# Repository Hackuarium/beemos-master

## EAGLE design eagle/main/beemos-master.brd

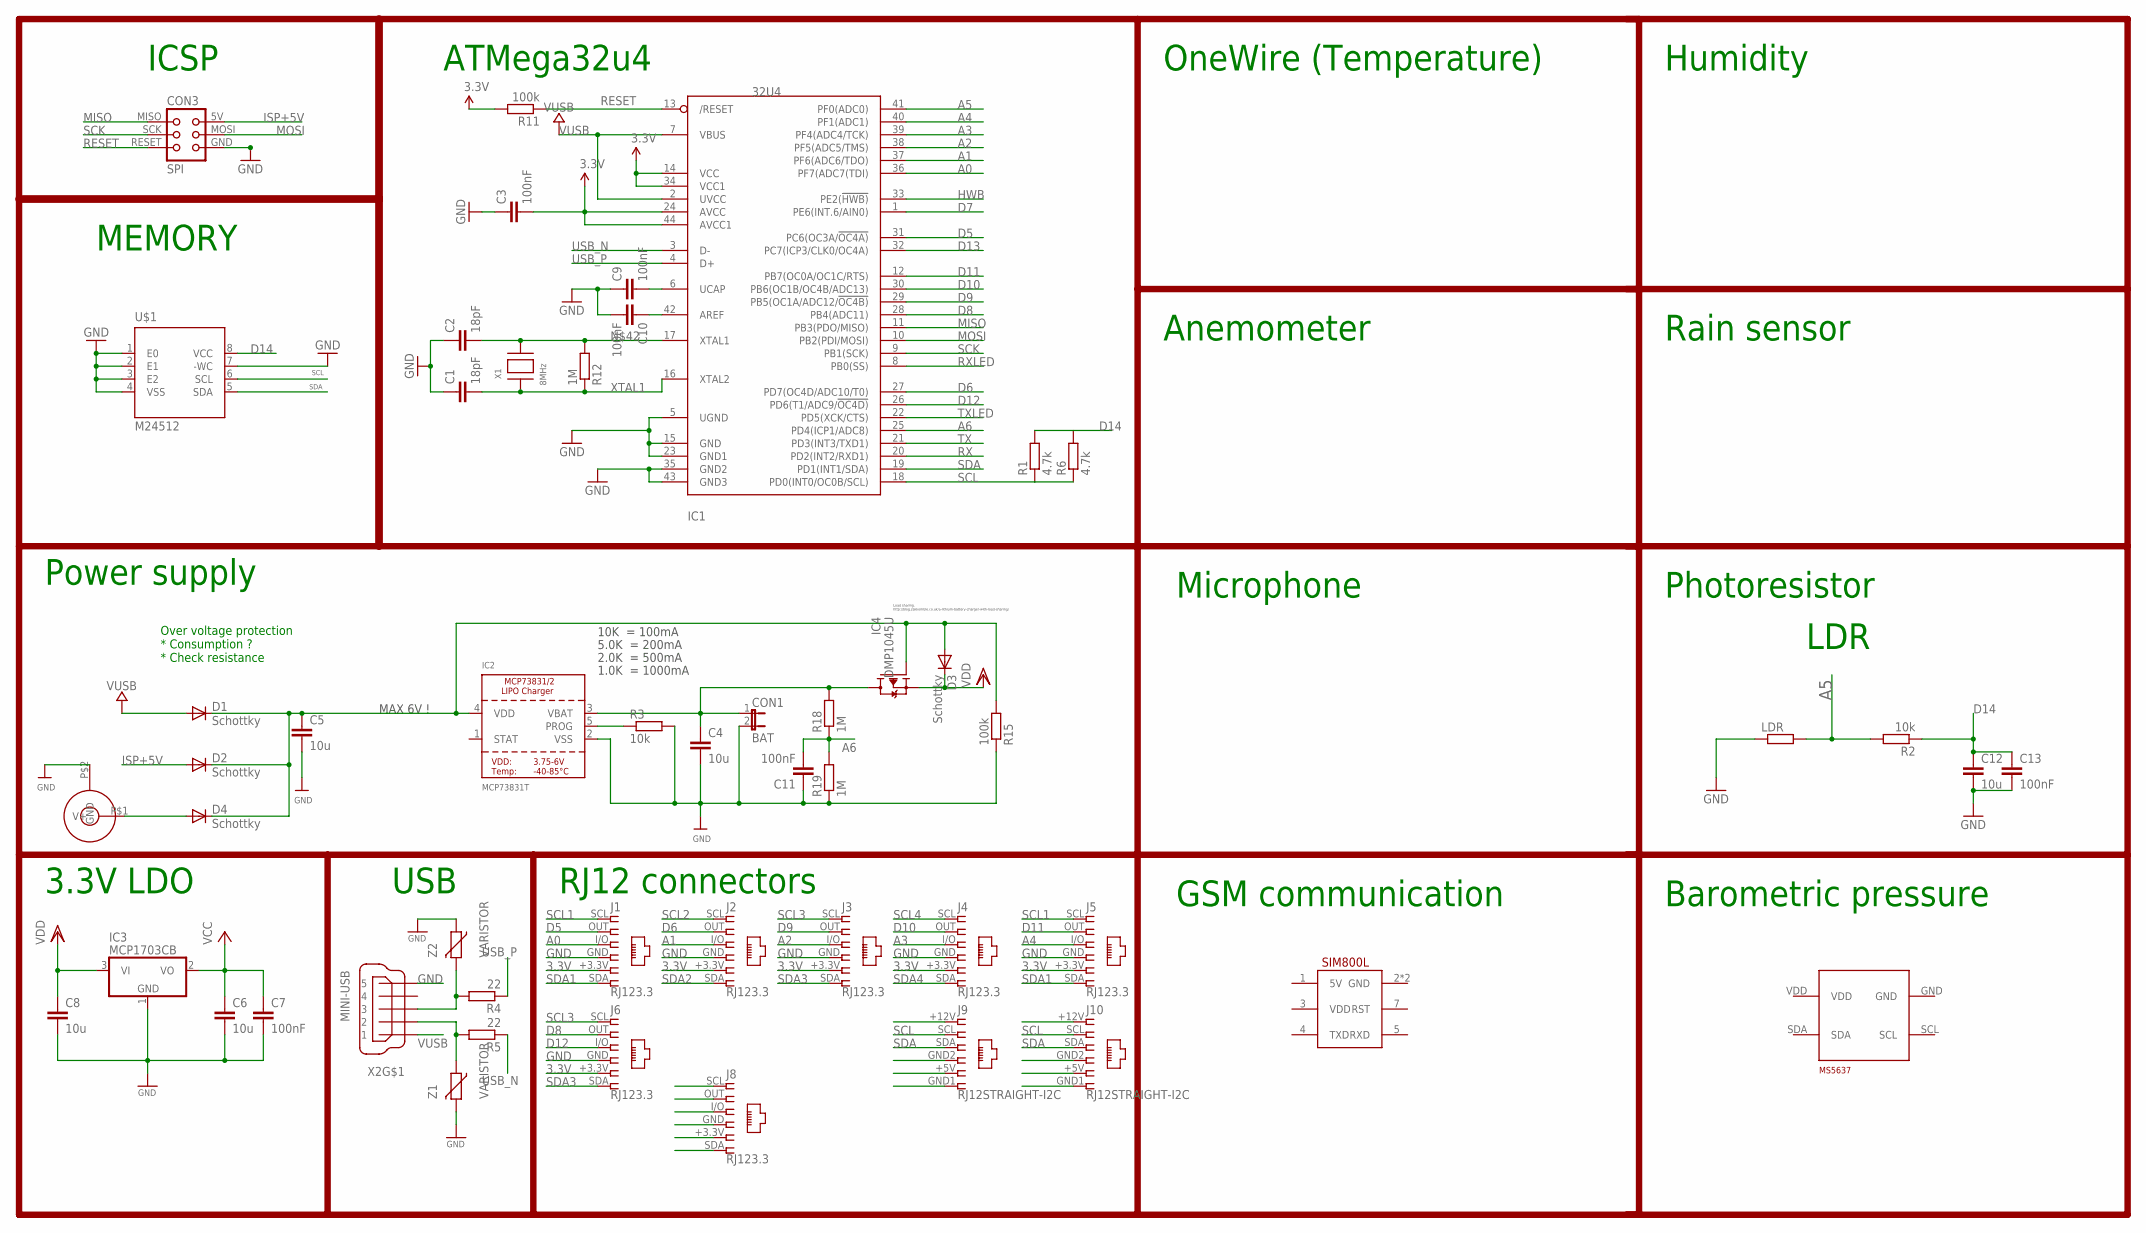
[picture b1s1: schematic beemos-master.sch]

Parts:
C1, C2: 18pF; C0805K; MPN 77-VJ1206A180JXXPBC; LCSC C1797
C3, C7, C9, C10, C11, C13: 100nF; C0805K; MPN 80-C1206C104K5R; LCSC C49678
C4, C5, C6, C8, C12: 10u; C0805K; MPN 77-VJ1206V106ZXQTBC; LCSC C15850
CON1: BAT; JP1
CON2: JACK_DC_BARREL; DC_BARREL
CON3: SPI; TC2030-MCP-NL
D1, D2, D3, D4: Schottky; SOD123; MPN 621-1N5819HW-F; LCSC C82544
IC1: 32U4; TQFP44; MPN 556-ATMEGA32U4RC-AU; LCSC C44854
IC2: MCP73831T; SOT23-5; MPN 579-MCP73831T-3ACIOT; LCSC C14879
IC3: MCP1703CB; SOT23; LCSC C53352
IC4: DMP1045U; SOT-23; MPN 621-DMP1045U-7; LCSC C96613
J1, J2, J3, J4, J5, J6, J8: RJ123.3; RJ12-STRAIGHT-3.3
J9, J10: RJ12STRAIGHT-I2C; RJ12-STRAIGHT-I2C
LDR: R-EU_0207/2V; 0207/2V
R1, R6: 4.7k; R0805
R2: 10k; R0805; MPN RC1206FR-07100KL; LCSC C17407
R3: 10k; R0805; LCSC C17414
R4, R5: 22; R0805; LCSC C17561
R11, R15: 100k; R0805; MPN RC1206FR-07100KL; LCSC C17407
R12, R18, R19: 1M; R0805; LCSC C17514
U$1: M24512; SO8
U$6: SIM800L; SIP
U$7: MS5637
X1: 8MHz; NX6035; MPN 729-F60800010; LCSC C122522
X2: MINI-USB; 32005-201; MPN 649-10033526-N3212LF; LCSC C46391
Z1, Z2: VARISTOR; CT/CN0805; LCSC C79709

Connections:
3.3V: C3.2, C6.1, C7.1, IC1.14 (VCC), IC1.24 (AVCC), IC1.34 (VCC1), IC1.44 (AVCC1), IC3.2 (VO), J1.+3.3V (5), J2.+3.3V (5), J3.+3.3V (5), J4.+3.3V (5), J5.+3.3V (5), J6.+3.3V (5), R11.2
A0: IC1.36 (PF7(ADC7(TDI)), J1.I/O (3)
A1: IC1.37 (PF6(ADC6/TDO)), J2.I/O (3)
A2: IC1.38 (PF5(ADC5/TMS)), J3.I/O (3)
A3: IC1.39 (PF4(ADC4/TCK)), J4.I/O (3)
A4: IC1.40 (PF1(ADC1)), J5.I/O (3)
A5: IC1.41 (PF0(ADC0)), LDR.2, R2.2
A6: C11.2, IC1.25 (PD4(ICP1/ADC8)), R18.1, R19.2
AREF: C10.1, IC1.42 (AREF)
D5: IC1.31 (PC6(OC3A/!OC4A)), J1.OUT (2)
D6: IC1.27 (PD7(OC4D/ADC10/T0)), J2.OUT (2)
D7: IC1.1 (PE6(INT.6/AIN0))
D8: IC1.28 (PB4(ADC11)), J6.OUT (2)
D9: IC1.29 (PB5(OC1A/ADC12/!OC4B)), J3.OUT (2)
D10: IC1.30 (PB6(OC1B/OC4B/ADC13)), J4.OUT (2)
D11: IC1.12 (PB7(OC0A/OC1C/RTS)), J5.OUT (2)
D12: IC1.26 (PD6(T1/ADC9/!OC4D)), J6.I/O (3)
D13: IC1.32 (PC7(ICP3/CLK0/OC4A))
D14: C12.1, C13.1, R1.2, R2.1, R6.2, U$1.8 (VCC)
GND: C1.1, C2.1, C3.1, C4.2, C5.2, C6.2, C7.2, C8.2, C9.1, C10.2, C11.1, C12.2, C13.2, CON1.2, CON2.P$2 (GND), CON3.GND, IC1.5 (UGND), IC1.15 (GND), IC1.23 (GND1), IC1.35 (GND2), IC1.43 (GND3), IC2.2 (VSS), IC3.1 (GND), J1.GND (4), J2.GND (4), J3.GND (4), J4.GND (4), J5.GND (4), J6.GND (4), LDR.1, R3.2, R15.1, R19.1, U$1.1 (E0), U$1.2 (E1), U$1.3 (E2), U$1.4 (VSS), U$1.7 (-WC), X2.5, Z1.2, Z2.1
HWB: IC1.33 (PE2(!HWB))
ISP+5V: CON3.5V (VCC), D2.A
MISO: CON3.MISO, IC1.11 (PB3(PDO/MISO))
MOSI: CON3.MOSI, IC1.10 (PB2(PDI/MOSI))
unnamed: C9.2, IC1.6 (UCAP)
unnamed: CON2.P$1 (V+), D4.A
unnamed: IC2.5 (PROG), R3.1
unnamed: C5.1, D1.C, D2.C, D3.A, D4.C, IC2.4 (VDD), IC4.1 (G), R15.2
unnamed: C2.2, IC1.17 (XTAL1), R12.2, X1.P$2
RESET: CON3.RESET, IC1.13 (/RESET), R11.1
RX: IC1.20 (PD2(INT2/RXD1))
RXLED: IC1.8 (PB0(SS))
SCK: CON3.SCK, IC1.9 (PB1(SCK))
SCL: IC1.18 (PD0(INT0/OC0B/SCL)), J9.SCL (2), J10.SCL (2), R1.1, R6.1, U$1.6 (SCL)
SCL1: J1.SCL (1), J5.SCL (1)
SCL2: J2.SCL (1)
SCL3: J3.SCL (1), J6.SCL (1)
SCL4: J4.SCL (1)
SDA: IC1.19 (PD1(INT1/SDA)), J9.SDA (3), J10.SDA (3), U$1.5 (SDA)
SDA1: J1.SDA (6), J5.SDA (6)
SDA2: J2.SDA (6)
SDA3: J3.SDA (6), J6.SDA (6)
SDA4: J4.SDA (6)
TX: IC1.21 (PD3(INT3/TXD1))
TXLED: IC1.22 (PD5(XCK/CTS))
USBC_N: R5.2, X2.2, Z1.1
USBC_P: R4.2, X2.3, Z2.2
USB_N: IC1.3 (D-), R5.1
USB_P: IC1.4 (D+), R4.1
VBAT1: C4.1, CON1.1, IC2.3 (VBAT), IC4.3 (D), R18.2
VDD: C8.1, D3.C, IC3.3 (VI), IC4.2 (S)
VUSB: D1.A, IC1.2 (UVCC), IC1.7 (VBUS), X2.1
XTAL1: C1.2, IC1.16 (XTAL2), R12.1, X1.P$1

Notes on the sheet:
USB
ICSP
ATMega32u4
3.3V LDO
10K = 100mA
5.0K = 200mA
2.0K = 500mA
1.0K = 1000mA
MAX 6V !
Load sharing: http://blog.zakkemble.co.uk/a-lithium-battery-charger-with-load-sharing/
RJ12 connectors
Over voltage protection * Consumption ? * Check resistance
Power supply
OneWire (Temperature)
Anemometer
Microphone
LDR
MEMORY
Photoresistor
GSM communication
Barometric pressure
Rain sensor
Humidity

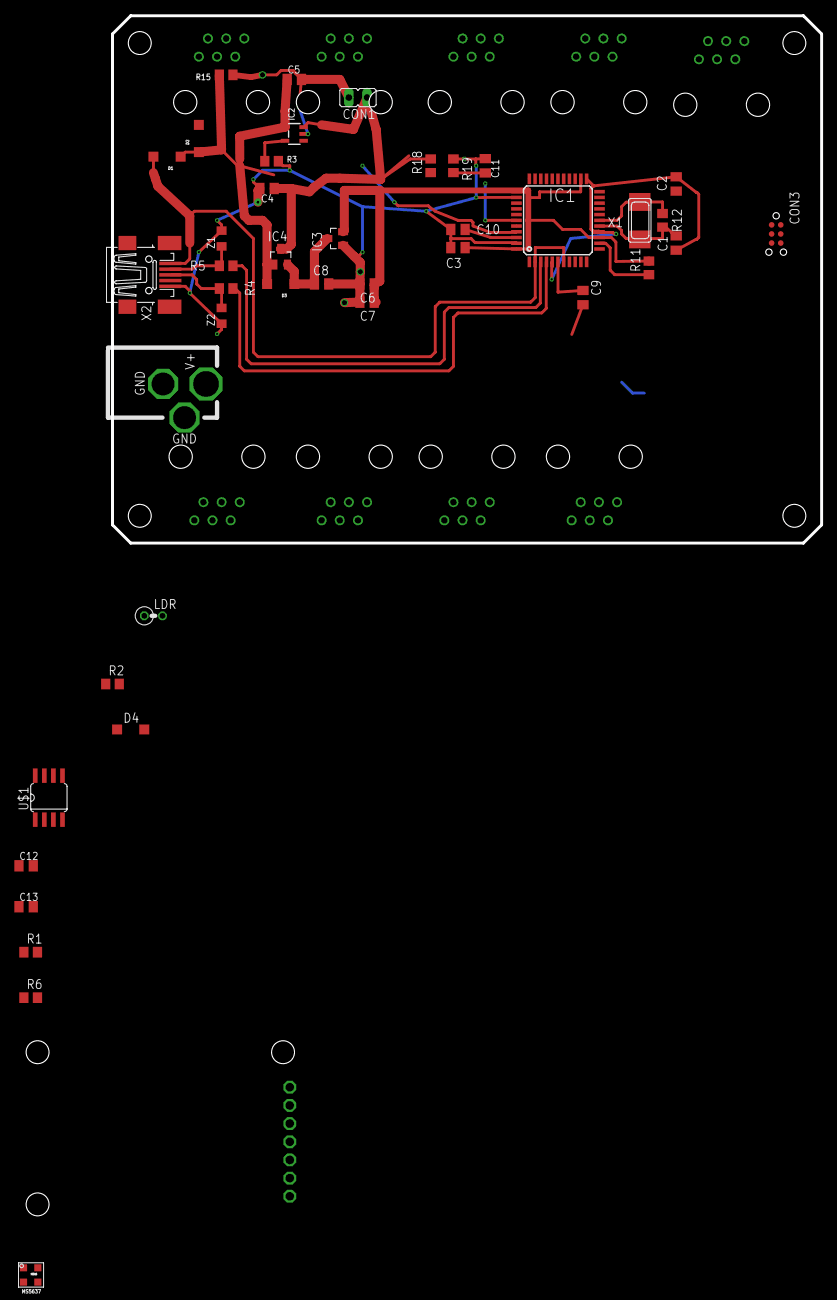
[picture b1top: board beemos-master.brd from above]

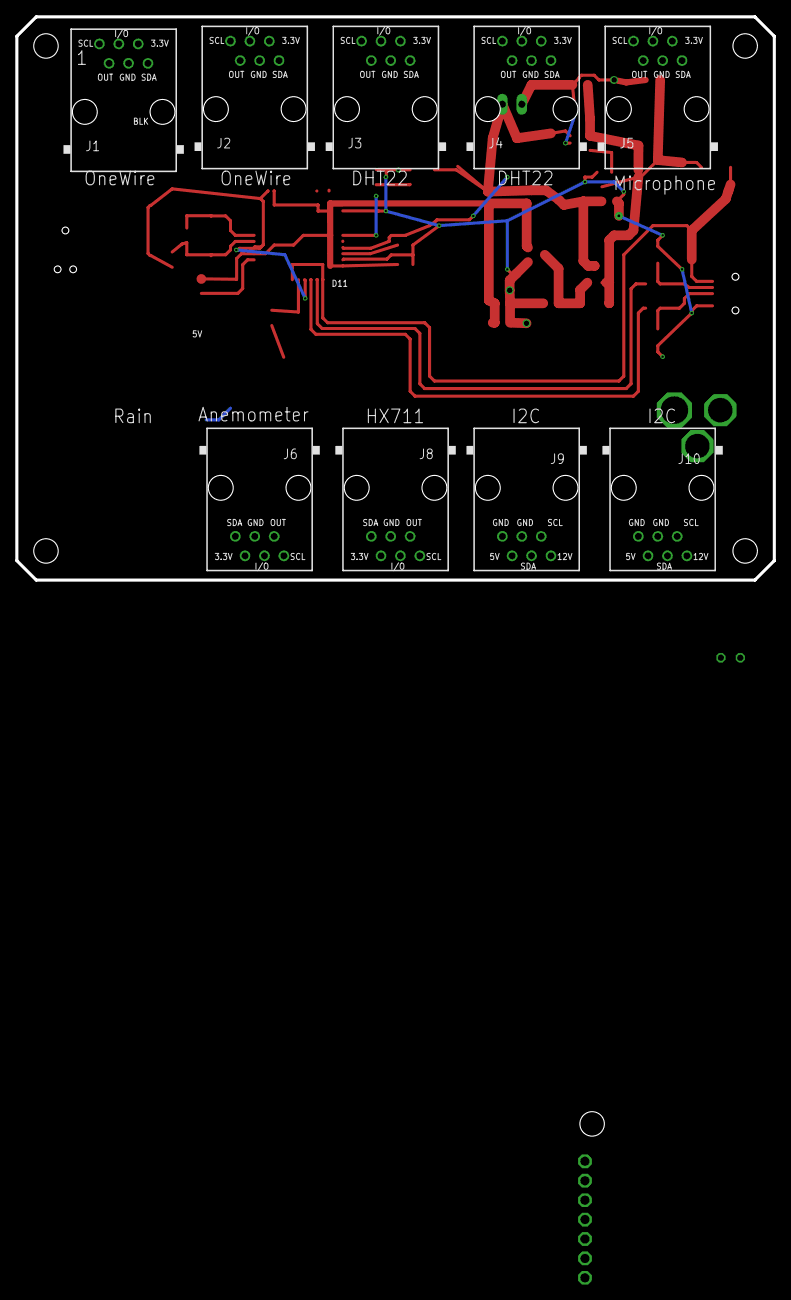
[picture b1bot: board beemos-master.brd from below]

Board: 2 copper layers, 99.1 x 73.7 mm, 52 parts (9 on the bottom side), 42 nets.

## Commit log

2018-04-14 add gitignore
2018-04-14 working on PCB
2018-04-17 Added modules to schematics
2018-04-19 Placed SIM800L module, added connections in schematic

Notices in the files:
parts and their libraries:
lpatiny: ©2009 ROFA.cz - modified and updated by Robert Darlington ‹rdarlington@gmail.com›
microbuilder: This work is placed in the public domain, and may be freely used for commercial and non-commercial work with the following conditions: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
